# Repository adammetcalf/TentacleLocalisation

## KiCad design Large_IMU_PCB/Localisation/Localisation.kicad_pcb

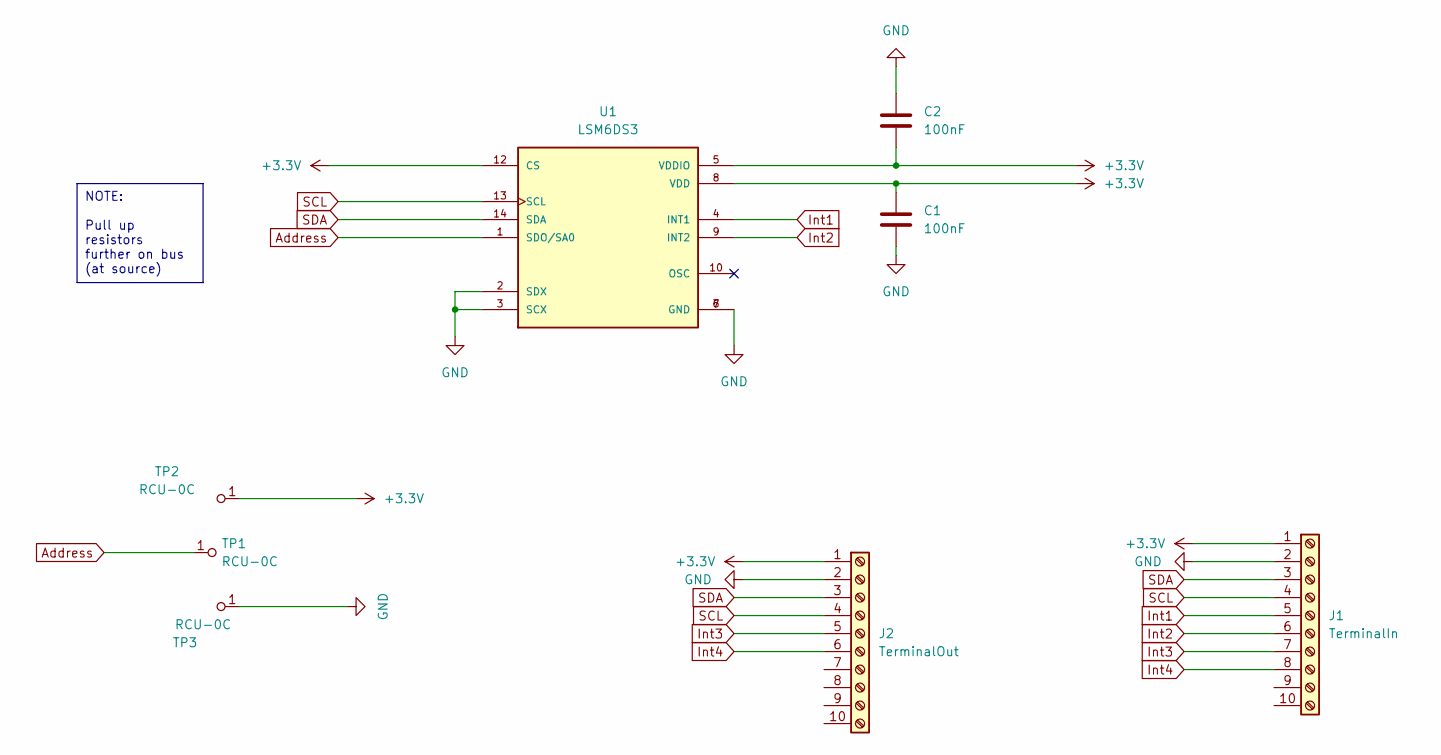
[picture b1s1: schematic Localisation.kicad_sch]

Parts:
C1, C2: 100nF; C_0201_0603Metric
J1: TerminalIn; TerminalBlock_Phoenix_MKDS-1,5-10_1x10_P5.00mm_Horizontal
J2: TerminalOut; TerminalBlock_Phoenix_MKDS-1,5-10_1x10_P5.00mm_Horizontal
TP1, TP2, TP3: RCU-0C; PROBE_PAD_0603; MPN RCU-0C; Digi-Key_PN A106145CT-ND
U1: LSM6DS3; PQFN50P300X250X86-14N; PARTREV 2

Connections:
+3.3V: C1.1, C2.2, J1.1, J2.1, TP2.1, U1.5 (VDDIO), U1.8 (VDD), U1.12 (CS)
Address: TP1.1, U1.1 (SDO/SA0)
GND: C1.2, C2.1, J1.2, J2.2, TP3.1, U1.2 (SDX), U1.3 (SCX), U1.6 (GND), U1.7 (GND)
Int1: J1.5, U1.4 (INT1)
Int2: J1.6, U1.9 (INT2)
Int3: J1.7, J2.5
Int4: J1.8, J2.6
SCL: J1.4, J2.4, U1.13 (SCL)
SDA: J1.3, J2.3, U1.14 (SDA)

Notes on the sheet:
NOTE: Pull up resistors further on bus (at source)

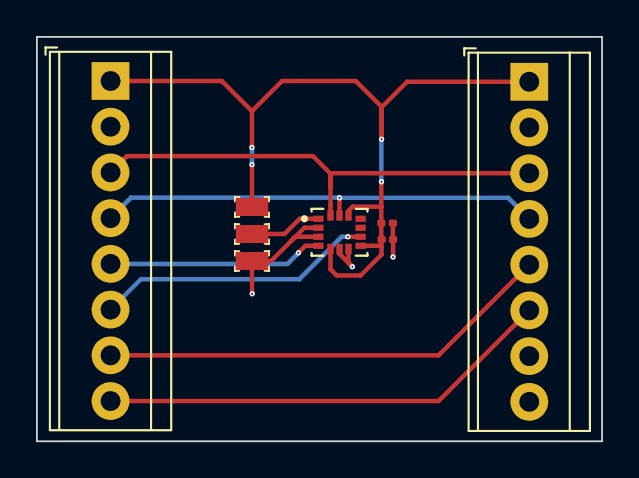
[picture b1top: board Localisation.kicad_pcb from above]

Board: 2 copper layers, 31.4 x 22.5 mm, 8 parts (0 on the bottom side), 9 nets.

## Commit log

2024-01-17 Added PCB design for large board (IMU) - proof of concept stage 1.
2024-01-18 Added Teensy code for Hall Effects Sensor Interaction (MLX90393)
